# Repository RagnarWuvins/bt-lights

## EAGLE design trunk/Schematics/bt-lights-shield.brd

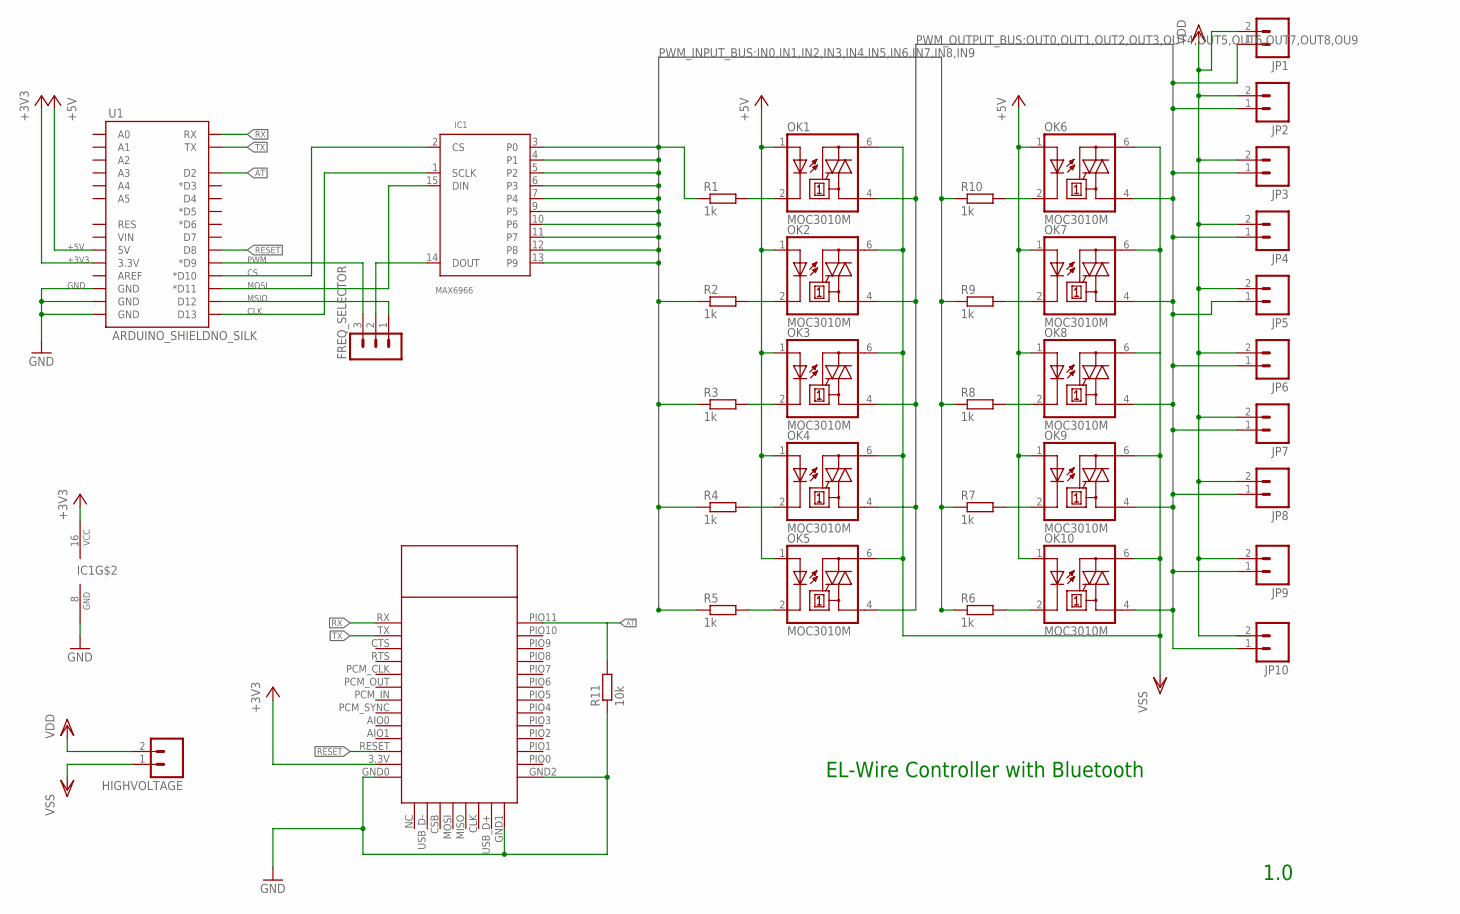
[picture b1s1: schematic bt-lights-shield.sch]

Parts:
FREQ_SELECTOR: MA03-1
HC0305: HC0305
HIGHVOLTAGE: M02-JST-2MM-SMT; JST-2-SMD
IC1: MAX6966; QSOP16
JP1, JP2, JP3, JP4, JP5, JP6, JP7, JP8, JP9, JP10: M02-JST-2MM-SMT; JST-2-SMD
OK1, OK2, OK3, OK4, OK5, OK6, OK7, OK8, OK9, OK10: MOC3010M; DIL06
R1, R2, R3, R4, R5, R6, R7, R8, R9, R10: 1k; R1206
R11: 10k; R1206
U1: ARDUINO_SHIELDNO_SILK; DUEMILANOVE_VIAS

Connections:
+3V3: HC0305.3.3V, IC1.16 (VCC), U1.3.3V
+5V: OK1.1 (A), OK2.1 (A), OK3.1 (A), OK4.1 (A), OK5.1 (A), OK6.1 (A), OK7.1 (A), OK8.1 (A), OK9.1 (A), OK10.1 (A), U1.5V
AT: HC0305.PIO11, R11.2, U1.D2
CLK: IC1.1 (SCLK), U1.D13
CS: IC1.2 (CS), U1.D10 (*D10)
GND: HC0305.GND0, HC0305.GND1, HC0305.GND2, IC1.8 (GND), R11.1, U1.GND@0 (GND), U1.GND@1 (GND), U1.GND@2 (GND)
IN0: IC1.3 (P0), R1.1
IN1: IC1.4 (P1), R2.1
IN2: IC1.5 (P2), R3.1
IN3: IC1.6 (P3), R4.1
IN4: IC1.7 (P4), R5.1
IN5: IC1.9 (P5), R10.1
IN6: IC1.10 (P6), R9.1
IN7: IC1.11 (P7), R8.1
IN8: IC1.12 (P8), R7.1
IN9: IC1.13 (P9), R6.1
MOSI: IC1.15 (DIN), U1.D11 (*D11)
MSIO: FREQ_SELECTOR.1, U1.D12
unnamed: OK1.2 (C), R1.2
unnamed: OK10.2 (C), R6.2
unnamed: OK9.2 (C), R7.2
unnamed: OK8.2 (C), R8.2
unnamed: OK7.2 (C), R9.2
unnamed: OK6.2 (C), R10.2
unnamed: OK2.2 (C), R2.2
unnamed: OK3.2 (C), R3.2
unnamed: OK4.2 (C), R4.2
unnamed: OK5.2 (C), R5.2
unnamed: FREQ_SELECTOR.2, IC1.14 (DOUT)
OUT0: JP1.1 (2), OK1.4 (A1)
OUT1: JP2.1 (2), OK2.4 (A1)
OUT2: JP3.1 (2), OK3.4 (A1)
OUT3: JP4.1 (2), OK4.4 (A1)
OUT4: JP5.1 (2), OK5.4 (A1)
OUT5: JP6.1 (2), OK6.4 (A1)
OUT6: JP7.1 (2), OK7.4 (A1)
OUT7: JP8.1 (2), OK8.4 (A1)
OUT8: JP9.1 (2), OK9.4 (A1)
OUT9: JP10.1 (2), OK10.4 (A1)
PWM: FREQ_SELECTOR.3, U1.D9 (*D9)
RESET: HC0305.RESET, U1.D8
RX: HC0305.RX, U1.RX
TX: HC0305.TX, U1.TX
VDD: HIGHVOLTAGE.2 (1), JP1.2 (1), JP2.2 (1), JP3.2 (1), JP4.2 (1), JP5.2 (1), JP6.2 (1), JP7.2 (1), JP8.2 (1), JP9.2 (1), JP10.2 (1)
VSS: HIGHVOLTAGE.1 (2), OK1.6 (A2), OK2.6 (A2), OK3.6 (A2), OK4.6 (A2), OK5.6 (A2), OK6.6 (A2), OK7.6 (A2), OK8.6 (A2), OK9.6 (A2), OK10.6 (A2)

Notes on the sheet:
EL-Wire Controller with Bluetooth
1.0

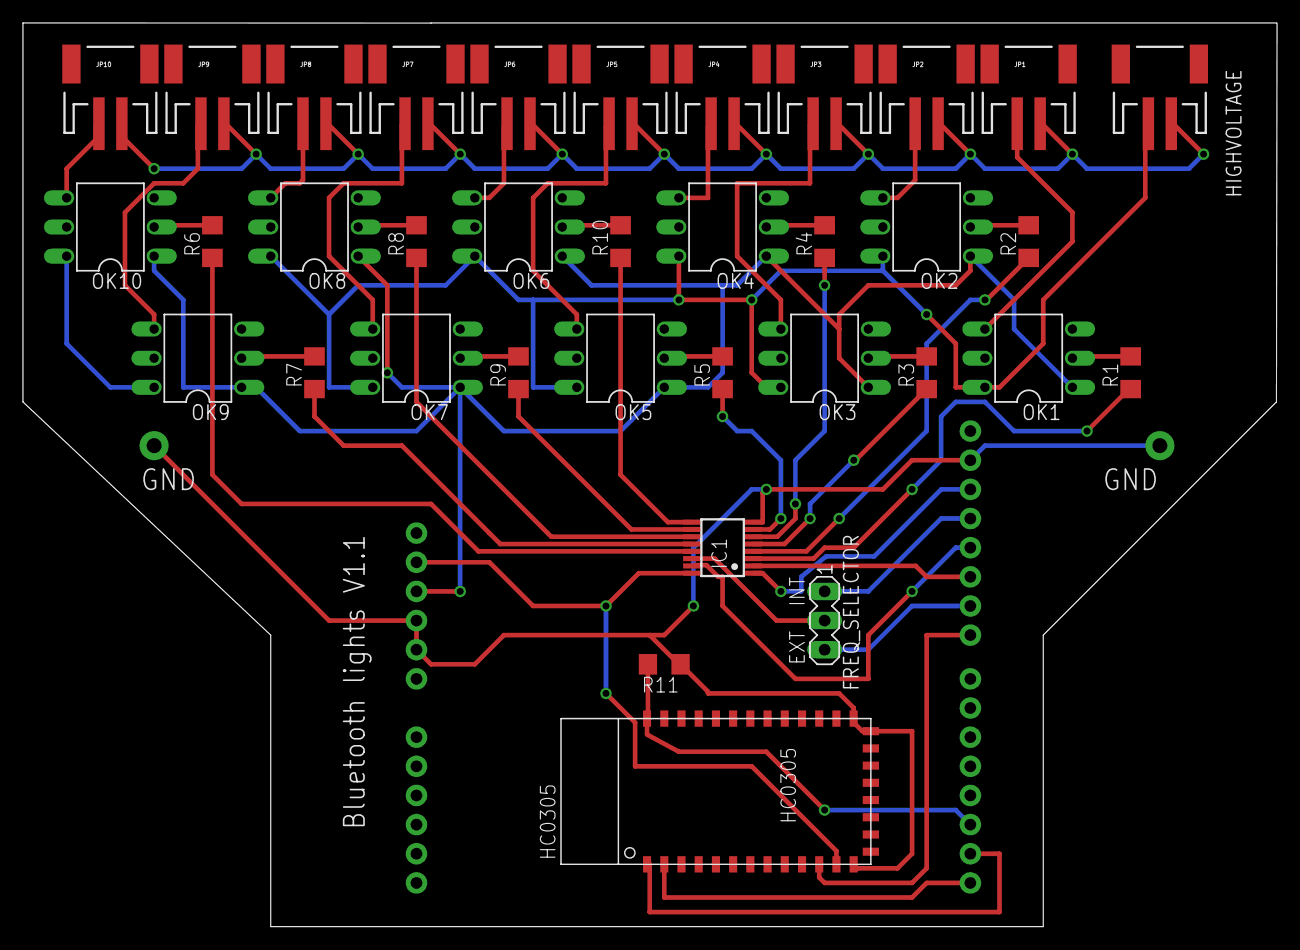
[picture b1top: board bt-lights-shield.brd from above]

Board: 2 copper layers, 109.3 x 78.7 mm, 36 parts (0 on the bottom side), 45 nets.

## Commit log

2012-01-21 Initial directory structure.
2012-01-21 ADDED: - project files for netduino and Arduino - schematics - Simulations - datasheets for Documentation
2012-01-21 Created wiki page through web user interface.
2012-01-21 DOCUMENTATION: - test for local wiki modifications
2012-01-21 Edited wiki page mainBTlights through web user interface.
2012-01-21 Edited wiki page sideBar through web user interface.
2012-01-21 Edited wiki page doumentationBTProtocol through web user interface.
2012-01-21 UPDATE: - wiki documentation update
2012-01-21 UPDATE: - documentation switch to UNIX
2012-01-25 ADDED: - Triac Test for Netduino
2012-02-03 ADDED: - Documentation for several parts - Pinning for the MAX6966 daughter PCB UPDATE: - Test routines for triacs, spi and bt (SPI test has class for strings)
2012-02-05 UPDATE: - changed folder structure - renamed test suite to bt-lights which will be the main (and only) program DELETED: - severeal test files (triac test)
2012-02-05 CLEAN UP: - deleted several unneeded files
    WARNING!!! THIS IS NOT A WORKING VERSION! PLEASE USE NEXT VERSION!
2012-02-05 CLEAN UP: - deleted several unneeded files - should work now, well maybe some paths not :)
2012-02-05 UPDATE: - First complete (and working) implementation of all components - BTModule class added - Constants improved - first 2 modes implemented (on, off)
2012-02-08 ADDED: - BTModule.cs for BT communication - added the documentation for the hardware UPDATE: - Constants and Program improved
2012-02-18 ADDED: - Gui for testing - SplitCommand.cs class - Implemented command event
2012-03-08 UPDATE: - protocol for channels fully implemented (see documentation) - performance for commands improved - commands work biaaatch :)
2012-04-22 Check in before smashing everything in parts :P
2012-04-24 EVERYTHING WORKS BITCHES :)
2012-04-24 Fixed some remaining conflicts
2012-06-11 ADDED: - the world famous icon - new protocol revision - schematics and layout (prelim)
2012-06-11 UPDATE: - new hardware fix in schematic - new commands in test gui - new pinning documented ADDED: - NETDUINO schematic
2012-06-12 UPDATE: - schematics and board file ADDED: - board file for arduino shield
2012-06-12 ADDED: - Android project
2012-06-12 ADDED: - first Android files UPDATE: - icon fixed :)
2012-06-13 ADDED: - COding guides - First view activities for Android and some Bluetooth testing code UPDATED: - main window with buttons
2012-06-13 UPDATE: - wiki start side has been updated
2012-07-03 ADDED: - working android project
2012-07-03 CLEANUP: - clean up the init code for BT a bit. UPDATE: - added a preference setter and getter
2012-07-09 ADDED: - menu bar
2012-07-09 ADDED: - bt_menu was missing
2012-07-24 UPDATE: - impelemnted proper ring buffer for bluetooth module (no more missing commands) - Added some clock functions for system checks - Implemented XML generation for Constants.cs -> Android ADDED: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
2012-07-24 UPDATE: - first shitty implementation for Bluetooth sending. TODO: - Do it right with proper bluetooth protocol and threading - import XML from C# project
2012-07-24 ADDED: - constants.xml from C# with love
2012-07-24 UPDATE: - new design for shield
2012-07-24 WIKI UPDATE
2012-07-24 ADDED: - images for docu
2012-07-24 Images scaled
2012-07-24 images scaled AGAIN!
2012-07-25 UPDATE: - Added subfolders for android projects
2012-07-25 MOVED: - old BTLights to BTLights subfolder
2012-07-25 Imported Icons and stuff from old project
2012-07-25 Add to delete
2012-07-25 finally delete it
2012-07-28 UPDATE: - new code pieces for android services
2012-07-28 ADDED: - BLuetooth Service class
2012-07-28 Restored deleted classes
2012-07-30 UPDATE: - implemented "on the fly value change" - Added menu to startup app - added errorlog view - tested COMMANDS
2012-07-30 ADDED: - screenshots for documentatin
2012-09-10 Set value was missing in docu
2012-09-10 ADDED: - new activity and class for getting x and y coordinates to control the lights
2012-09-11 UPDATE: - error codes added
2012-09-11 DELETE: - old android sources
2012-09-15 UPDATE: - Fixed issues in Bluetooth service
2012-09-15 UPDATE: - new API for the Netduino firmware - new methods in Android project
2012-10-07 UPDATE:
    - updated to the new BTM222B
    - applied some tracing for release version
2012-11-26 UPDATE: - Added special event for the lamp communication - restructured protocoll handling
2012-12-23 VERSION: - new protocol, new gui elements
2013-03-28 UPDATE: - Improved speed of BTReceive - Added all PINS as definitions - Added Hex2Str to Convert.cs BUGFIX: - Fixed timer reset bug (timer were not clear but only the value set to 0) - Fixed double s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
2013-03-28 UPDATE: - Added assembly information for official release 1.0
2013-03-28 ADDED: - Added folder for releases
2013-03-28 TAGGED: - Official release 1.0 (Yay!)
2013-03-28 TAGGED: - cleanup of the mess here
2013-03-28 ADDED: - TestTools directory
2013-04-04 RENAME: - renamed all files
2013-04-04 ADDED: - new classes added - renamed errorview
2013-12-14 Complete reprogramming of app!
2013-12-15 Update App for setup view
2013-12-15 Added selection of BT modules
2013-12-16 Updated settings view Cleanup of BTService New artwork
2013-12-18 Update to binding service and NOTIFICATION Lamp handles now all the commands
2013-12-22 Function selector added
2013-12-23 Firmware Update: function setter and getter were missing improved channel behaviour updated error log entries fixed wrong assertions
    App:
    Implemented trace viewer
    Implemented function selector
2013-12-25 Started putting in string resources instead of fixed strings
2013-12-25 Added a GeneralNotification class to wrap notifications for different APIs
2013-12-25 Improved stability of connection and introduced the connection lost state
2013-12-29 CommandHandler: added missing acknowledges and edited the return value to be correct Frame: added Value and channel setter and getter MAX6966: Daniela found a driver problem :| still trying to find o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
2015-03-27 Migrating wiki contents from Google Code

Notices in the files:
parts and their libraries:
SparkFun-Boards: Licensing: CC v3.0 Share-Alike You are welcome to use this library for commercial purposes.
